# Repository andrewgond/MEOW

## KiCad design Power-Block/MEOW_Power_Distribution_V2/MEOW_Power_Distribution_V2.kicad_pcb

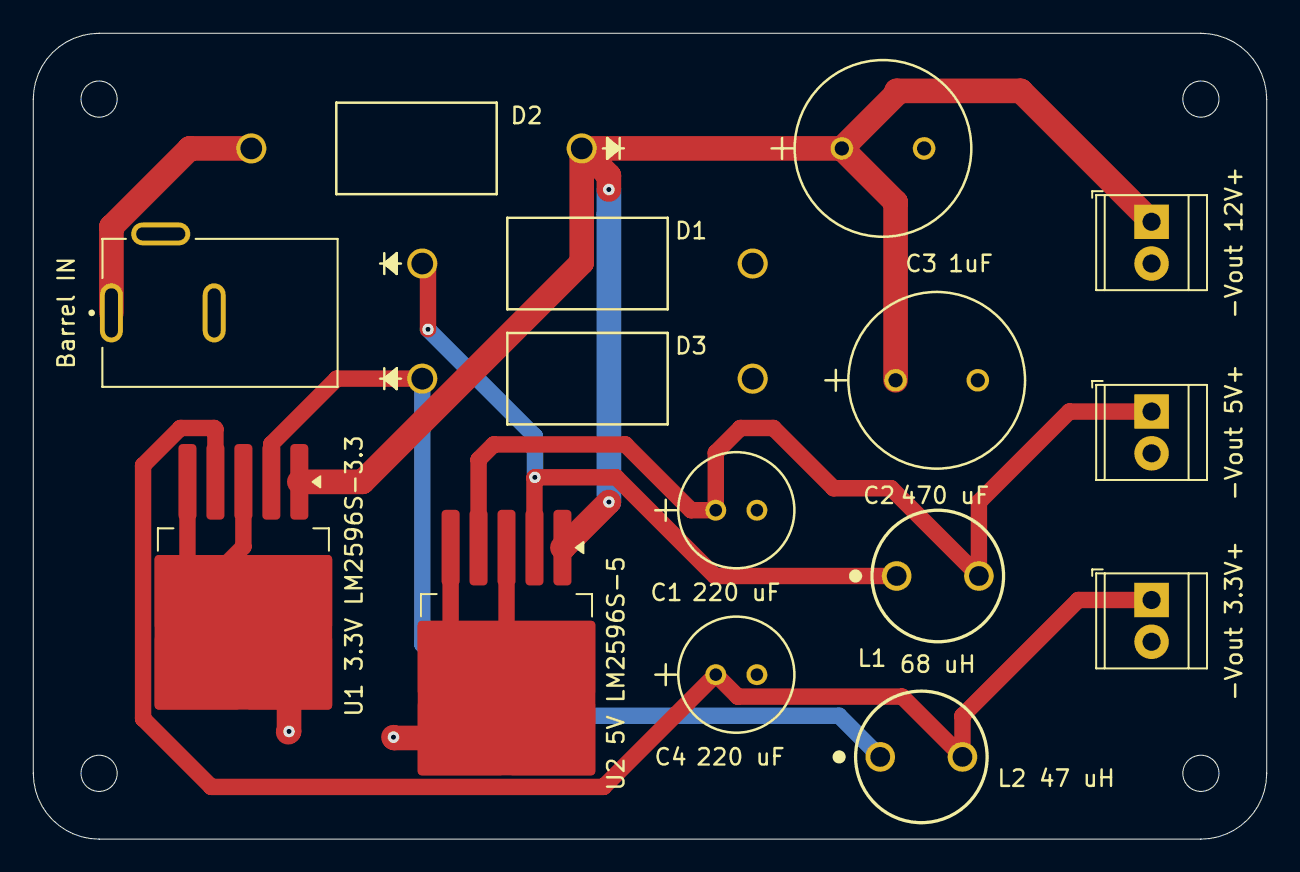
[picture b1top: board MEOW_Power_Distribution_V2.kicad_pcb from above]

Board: 2 copper layers, 75.0 x 49.0 mm, 19 parts (0 on the bottom side), 7 nets.

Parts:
Barrel IN: 54-00166; TENSILITY_54-00166
C1, C4: 220 uF; CAP_YX_6P3X11_RUB
C2: 470 uF; CAP_YX_10X12P5_RUB
C3: 1uF; CAP_YX_10X12P5_RUB
D1, D2, D3: 1N5820; CR_0-E3&slash_54_VIS
H1, H2, H3, H4: MountingHole; MountingHole_2.2mm_M2
J3, J4, J6: Terminal Out (Screw); TerminalBlock_TE_282834-2_1x02_P2.54mm_Horizontal
L1: 68 uH; WE-TIS_8075
L2 47 uH: 47uH; WE-TIS_8075
U1 3.3V LM2596S-3.3: LM2596S-3.3; TO-263-5_TabPin3
U2 5V LM2596S-5: LM2596S-5; TO-263-5_TabPin3

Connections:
GND: Barrel IN.B, C1.2, C2.2, C3.2, C4.2, D1.2 (A), D3.2 (A), J3.2, J4.2, J6.2, U1 3.3V LM2596S-3.3.3 (GND), U1 3.3V LM2596S-3.3.5 (~ON/OFF), U2 5V LM2596S-5.3 (GND), U2 5V LM2596S-5.5 (~ON/OFF)
unnamed: D1.1 (K), L1.1, U2 5V LM2596S-5.2 (OUT)
unnamed: Barrel IN.A, D2.2 (A)
unnamed: D3.1 (K), L2 47 uH.1, U1 3.3V LM2596S-3.3.2 (OUT)
Vout_3.3V: C4.1, J6.1, L2 47 uH.2, U1 3.3V LM2596S-3.3.4 (FB)
Vout_5V: C1.1, J4.1, L1.2, U2 5V LM2596S-5.4 (FB)
Vout_12V: C2.1, C3.1, D2.1 (K), J3.1, U1 3.3V LM2596S-3.3.1 (VIN), U2 5V LM2596S-5.1 (VIN)

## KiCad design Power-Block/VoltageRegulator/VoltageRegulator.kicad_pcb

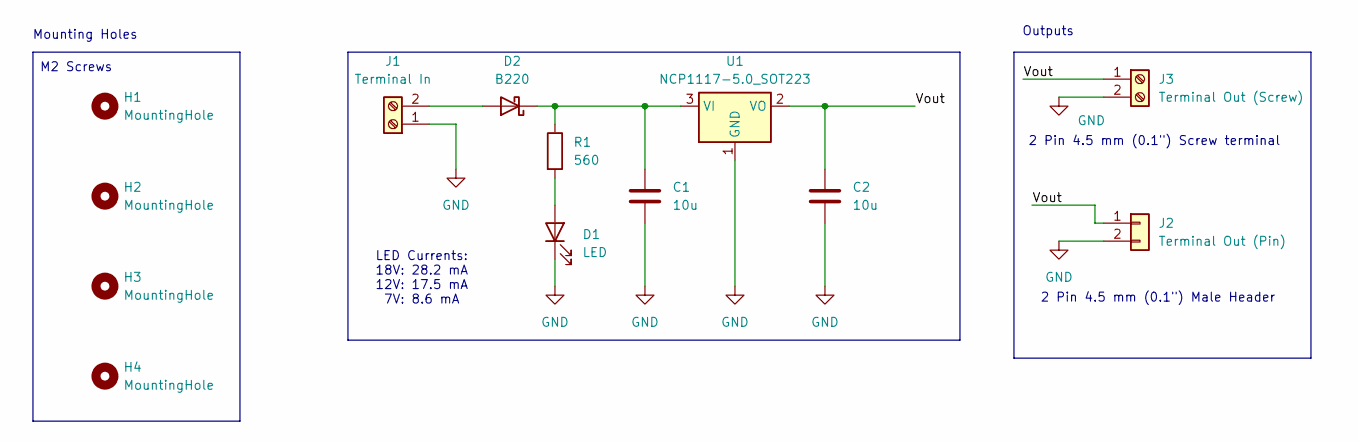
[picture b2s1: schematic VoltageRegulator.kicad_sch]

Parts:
C1, C2: 10u; C_1206_3216Metric
D1: LED; LED_0603_1608Metric
D2: B220; D_SMA
H1, H2, H3, H4: MountingHole; MountingHole_2.2mm_M2
J1: Terminal In; TerminalBlock_TE_282834-2_1x02_P2.54mm_Horizontal
J2: Terminal Out (Pin); PinHeader_1x02_P2.54mm_Vertical
J3: Terminal Out (Screw); TerminalBlock_TE_282834-2_1x02_P2.54mm_Horizontal
R1: 560; R_0805_2012Metric
U1: NCP1117-5.0_SOT223; SOT-223-3_TabPin2

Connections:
/Vout: C2.1, J2.1, J3.1, U1.2 (VO)
GND: C1.2, C2.2, D1.1 (K), J1.1, J2.2, J3.2, U1.1 (GND)
unnamed: D1.2 (A), R1.2
unnamed: D2.2 (A), J1.2
unnamed: C1.1, D2.1 (K), R1.1, U1.3 (VI)

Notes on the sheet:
Outputs
2 Pin 4.5 mm (0.1") Male Header
Mounting Holes
2 Pin 4.5 mm (0.1") Screw terminal
M2 Screws
LED Currents: 18V: 28.2 mA 12V: 17.5 mA 7V: 8.6 mA

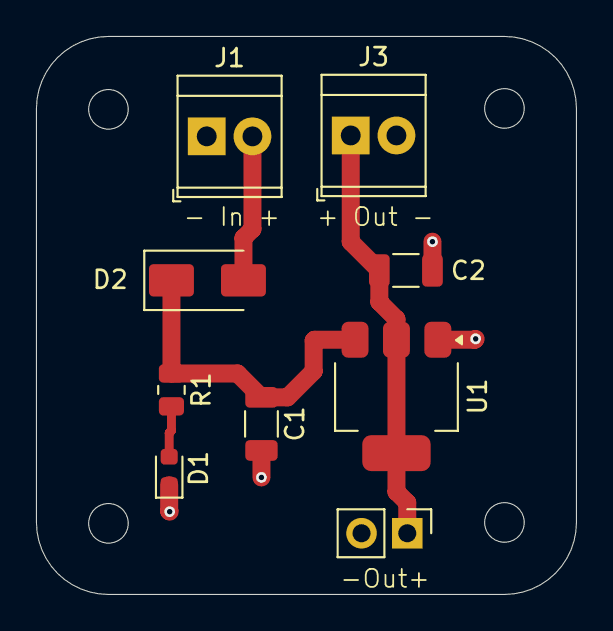
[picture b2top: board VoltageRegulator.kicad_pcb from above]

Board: 2 copper layers, 30.0 x 31.0 mm, 13 parts (0 on the bottom side), 5 nets.

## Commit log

2025-10-31 Added empty folders
2025-11-10 Power PCB and Schematic Updated
2025-11-12 Done with PCB
2025-11-12 Gerber File for JLC PCB
